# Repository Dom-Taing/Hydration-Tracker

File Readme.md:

# Hydration Tracker (Sensor + Display)

The goal of this product is to track how much water a user drink in a day. The sensor device would be a sleeve that can be worn onto a water bottle, it'll detect the water level in the bottle and convert that into volume of water. The display device would be a box where the gauge will measure if the user reach daily hydration goal. 

**Overall form factor (concept sketch):**
- **Sensor device:** sleeve that can be worn onto a water bottle (water level sensing + BLE)
- **Display device:** small desktop box with a water-drop window and NeoPixel gradient + top button

*The look and form factor of the product*

## Slide 2 — Sensor device (water level + BLE)

*The look and form factor of the Sensor device*

It's 4 rod containing the capacitive water level sensor connected with a stretchy fabric to wrap around the bottle.

### How it works
- The sensor device measures water level using a **No Contact Capacitive water level sensor**. 
- The **ESP32-C3** reads the digitized water level, filters noise, computes volume (consumed water), and save the data.
- It then sends updates to the display using **Bluetooth Low Energy (BLE)** when it's connected.

### Key parts (with part numbers)
- **Water sensor**: We'll be building our own using a copper strip + high value resistor + laminated sheets.
- **MCU**: [ESP32C3](datasheets/esp32-c3_datasheet_en.pdf)
- **Battery**: [Lipo Battery](datasheets/C101-_Li-Polymer_503562_1200mAh_3.7V_with_PCM_APPROVED_8.18.pdf)
---

## Slide 3 — Display device (NeoPixel gauge + Wi-Fi + button)

*The look and form factor of the display device*

### How it works
- The display device runs an **ESP32C3** that:
  1. Connects to the sensor over **BLE** to receive weight/consumption updates
  2. Move the **motor** to reflect current consumption toward daily goal
  3. Updates the **NeoPixel** gauge behind a water-drop window (green→yellow→red)
  4. Syncs daily usage to the cloud over **Wi-Fi** 
  5. Holding the **top button** will tare/calibrate the sensor for an empty bottle

### Key parts (with part numbers)
- **MCU**: [ESP32C3](datasheets/esp32-c3_datasheet_en.pdf)
- **LED gauge**: [XL-5050RGBC-WS2812B](datasheets/WS2812B.pdf)
- **Battery**: [Lipo Battery](datasheets/C101-_Li-Polymer_503562_1200mAh_3.7V_with_PCM_APPROVED_8.18.pdf)
- **Boost regulator**: [TPS61023](datasheets/tps61023.pdf)
- **Button**: [PTS636](datasheets/pts636.pdf)
- **Motor**: [28BYJ-48 – 5V Stepper Motor](datasheets/step-motor-5v-28byj48-datasheet.pdf)
---

## Slide 4 — Communication + system flow (2 figures)

### Figure A: Device communication (block diagram)

*Diagram displaying how the device communicates*

### Figure B: Detailed data flow (how the system works)

*Diagram displaying how the data flows in the system*

---

## Repo structure
- `README.md`
- `images/`
- `datasheets/`
  - (PDFs for each part)

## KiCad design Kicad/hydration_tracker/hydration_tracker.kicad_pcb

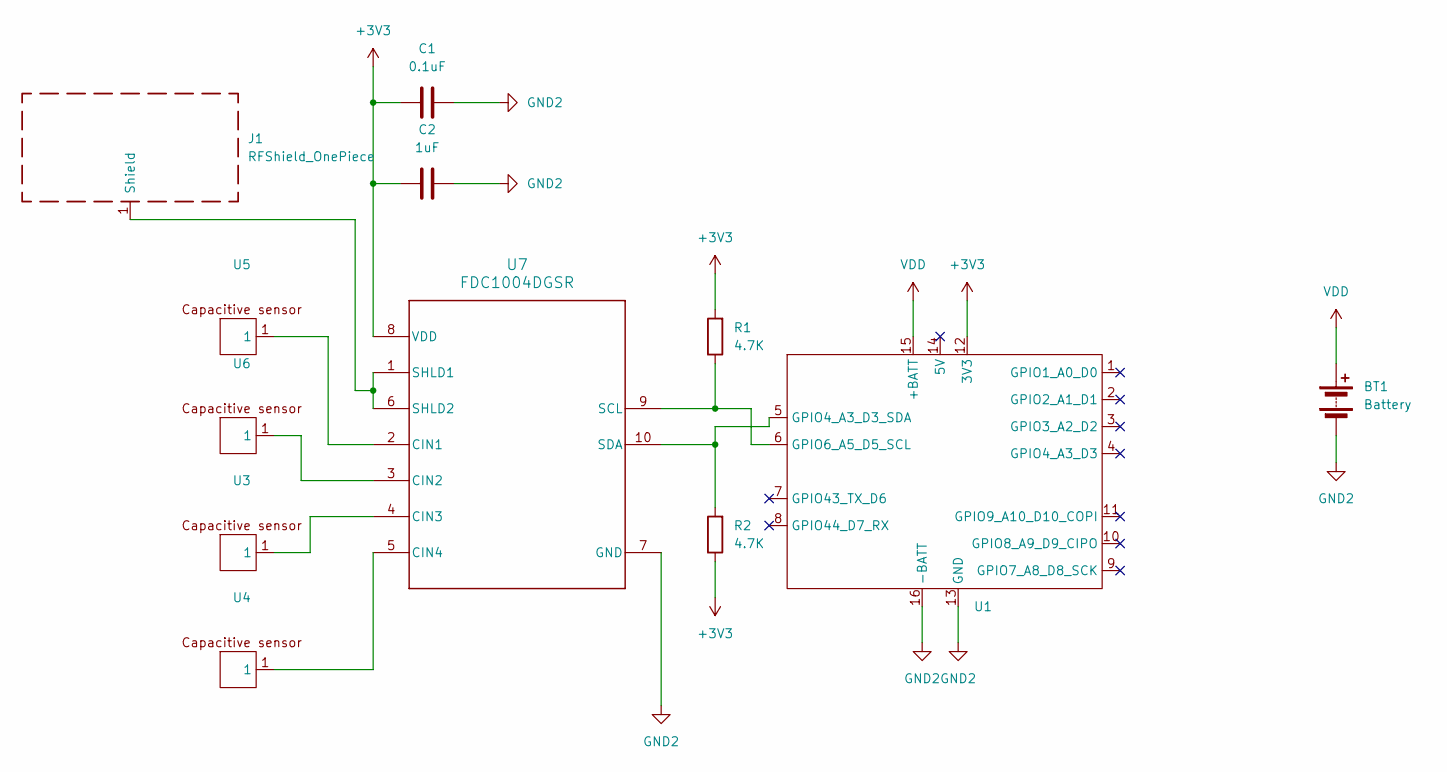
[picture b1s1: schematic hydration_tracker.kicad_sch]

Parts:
BT1: Battery; JST_PH_S2B-PH-K_1x02_P2.00mm_Horizontal
C1: 0.1uF; C_0805_2012Metric_Pad1.18x1.45mm_HandSolder
C2: 1uF; C_0805_2012Metric_Pad1.18x1.45mm_HandSolder
J1: RFShield_OnePiece; TestPoint_Pad_D1.0mm
R1, R2: 4.7K; R_0805_2012Metric_Pad1.20x1.40mm_HandSolder
U1: XIAO_ESP32
U3, U4, U5, U6: TestPoint_Pad_D1.0mm
U7: FDC1004DGSR; DGS0010A_M

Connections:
+3V3: C1.2, C2.1, R1.2, R2.1, U1.12 (3V3), U7.8 (VDD)
GND2: BT1.2 (-), C1.1, C2.2, U1.13 (GND), U1.16 (-BATT), U7.7 (GND)
unnamed: J1.1 (Shield), U7.1 (SHLD1), U7.6 (SHLD2)
unnamed: R2.2, U1.5 (GPIO4_A3_D3_SDA), U7.10 (SDA)
unnamed: R1.1, U1.6 (GPIO6_A5_D5_SCL), U7.9 (SCL)
unnamed: U3.1, U7.4 (CIN3)
unnamed: U4.1, U7.5 (CIN4)
unnamed: U5.1, U7.2 (CIN1)
unnamed: U6.1, U7.3 (CIN2)
VDD: BT1.1 (+), U1.15 (+BATT)

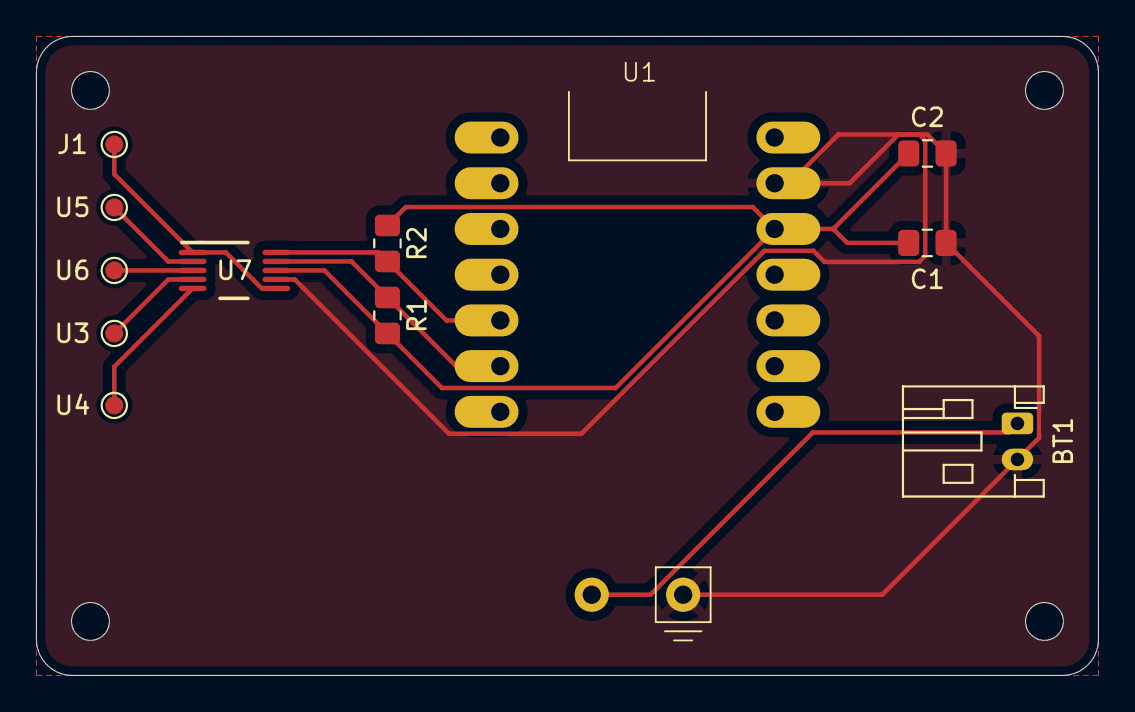
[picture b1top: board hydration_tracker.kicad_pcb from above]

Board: 2 copper layers, 59.0 x 35.5 mm, 12 parts (0 on the bottom side), 10 nets.

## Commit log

2026-01-18 New Repository
2026-01-19 finish read me
2026-01-27 Change to capacitive sensor
2026-01-27 adding kicad
2026-01-27 add label
2026-02-03 finish sensor pcb
2026-02-08 adding sensor
2026-02-08 add x27 motor
2026-02-09 add battery analysis
